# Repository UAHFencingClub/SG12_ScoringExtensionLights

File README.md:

# SG12_ScoringExtensionLights

A module for the [SG12 fencing scoring machine](https://www.blue-gauntlet.com/SG12-ST-MACHINE-w-score-and-time-and-remote_p_3799.html) that allows for 12V LED strips to be used as extension lights.

You can view the mirror on [CADLAB.io](https://cadlab.io/project/27194/main/files) if you want to see the schematic. < Needs to be updated, not sure why mirroring is not working.

# Wiring Diagram

Annocations and a wiring diagram can be found [here](Wiring.md)

# Parts (Haphazard)

Most things I got off amazon. I have not gotten all the connectors since not all are actually required. It depends on what you need. Look at the schematic to find out.

- IRF4905 MOSFET (Though probably most P Channel MOSFETs will do)
- Some sort of RJ45 (Ethernet) Connector (Don't get the ones with built in magnetics, those are usually a bit larger and are only for actual ethernet applications.
- Whatever 10k resistors you can find, the value really does not matter I would suggest something between 1k and 100k
- Some sort of barrel jack connector (Inner pin diameter of 2.1mm is more common than ones with 2.5mm inner pin diameter)
- PhoenixContact MSTBA 2,5 2-G-5,08 1x02 P5.08mm Horizontal
- Molex Mini-Fit Jr 5569 2x04 P4.20mm Horizontal
- Standard 2.54mm pin header

# Get PCBs

**Disclaimer: If ordering through their site, PCBWay will "donate 10% PCB and PCB assembly cost to" [me](https://github.com/QuantumEF)**

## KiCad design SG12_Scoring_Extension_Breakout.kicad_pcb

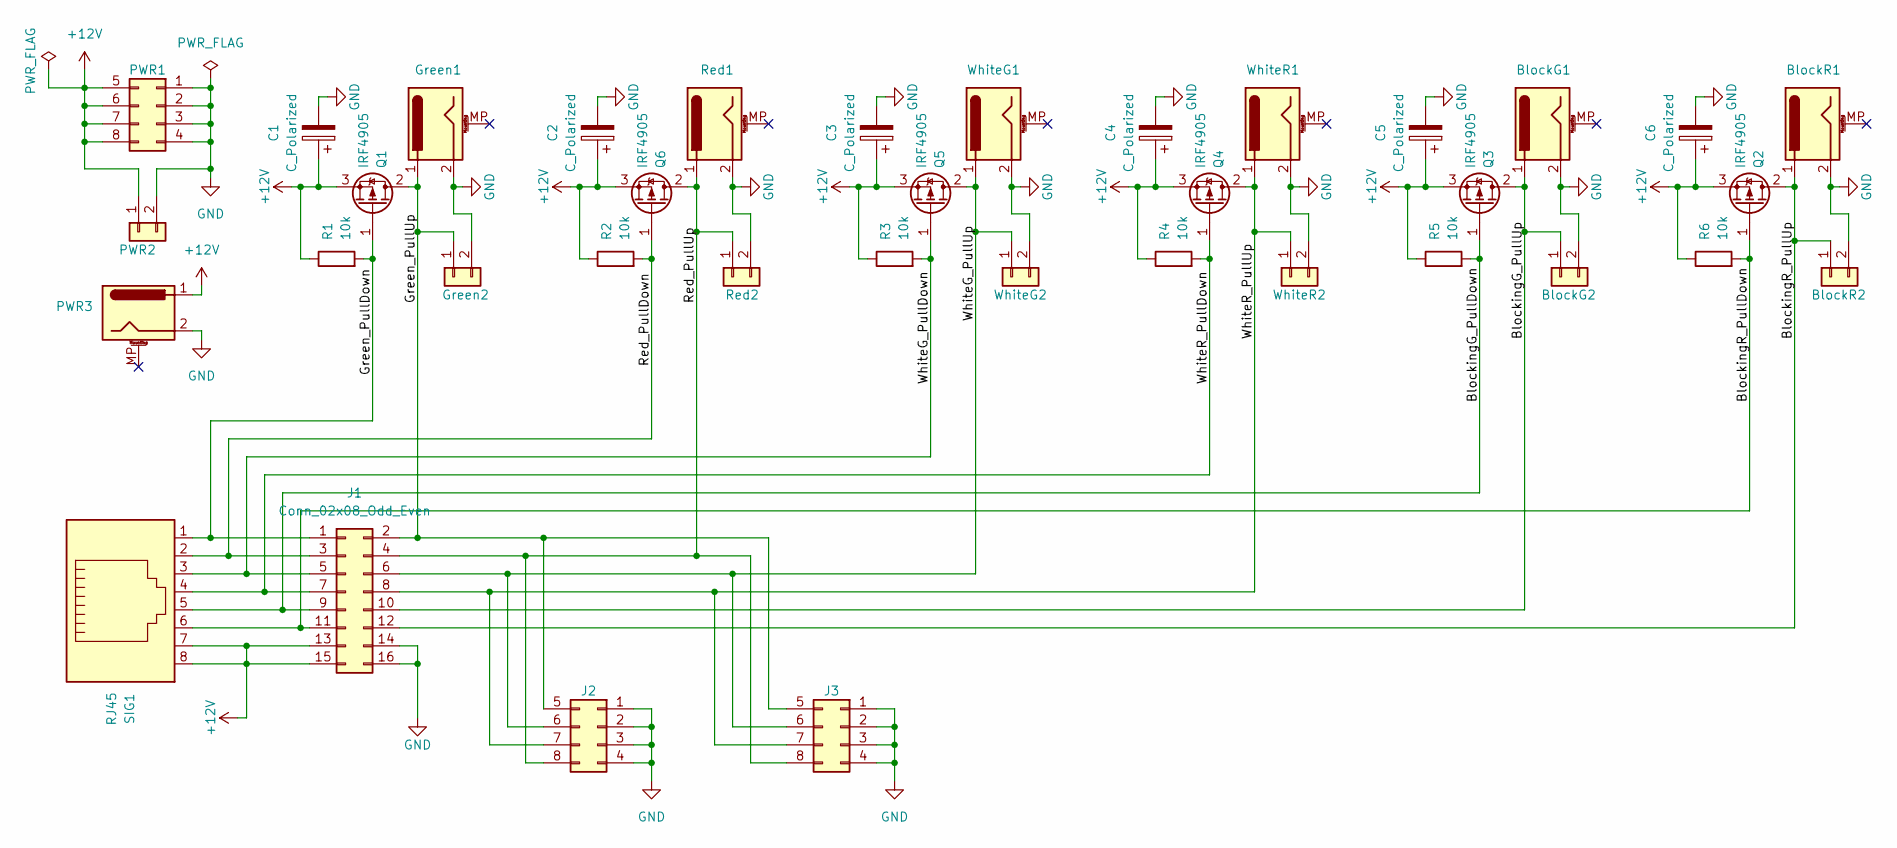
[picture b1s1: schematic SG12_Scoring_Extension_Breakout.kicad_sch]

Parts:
BlockG1: Barrel_Jack_MountingPin; BarrelJack_GCT_DCJ200-10-A_Horizontal
BlockG2: Conn_01x02; PhoenixContact_MSTBA_2,5_2-G-5,08_1x02_P5.08mm_Horizontal
BlockR1: Barrel_Jack_MountingPin; BarrelJack_GCT_DCJ200-10-A_Horizontal
BlockR2: Conn_01x02; PhoenixContact_MSTBA_2,5_2-G-5,08_1x02_P5.08mm_Horizontal
C1, C2, C3, C4, C5, C6: C_Polarized; CP_Radial_D6.3mm_P2.50mm
Green1: Barrel_Jack_MountingPin; BarrelJack_GCT_DCJ200-10-A_Horizontal
Green2: Conn_01x02; PhoenixContact_MSTBA_2,5_2-G-5,08_1x02_P5.08mm_Horizontal
J1: Conn_02x08_Odd_Even; PinHeader_2x08_P2.54mm_Vertical
J2, J3: Conn_02x04_Top_Bottom; Molex_Mini-Fit_Jr_5569-08A2_2x04_P4.20mm_Horizontal
PWR1: Conn_02x04_Top_Bottom; Molex_Mini-Fit_Jr_5569-08A2_2x04_P4.20mm_Horizontal
PWR2: Conn_01x02; PhoenixContact_MSTBA_2,5_2-G-5,08_1x02_P5.08mm_Horizontal
PWR3: Barrel_Jack_MountingPin; BarrelJack_GCT_DCJ200-10-A_Horizontal
Q1, Q2, Q3, Q4, Q5, Q6: IRF4905; TO-220-3_Vertical
R1, R2, R3, R4, R5, R6: 10k; R_Axial_DIN0207_L6.3mm_D2.5mm_P10.16mm_Horizontal
Red1: Barrel_Jack_MountingPin; BarrelJack_GCT_DCJ200-10-A_Horizontal
Red2: Conn_01x02; PhoenixContact_MSTBA_2,5_2-G-5,08_1x02_P5.08mm_Horizontal
SIG1: RJ45; RJ45_Amphenol_54602-x08_Horizontal
WhiteG1: Barrel_Jack_MountingPin; BarrelJack_GCT_DCJ200-10-A_Horizontal
WhiteG2: Conn_01x02; PhoenixContact_MSTBA_2,5_2-G-5,08_1x02_P5.08mm_Horizontal
WhiteR1: Barrel_Jack_MountingPin; BarrelJack_GCT_DCJ200-10-A_Horizontal
WhiteR2: Conn_01x02; PhoenixContact_MSTBA_2,5_2-G-5,08_1x02_P5.08mm_Horizontal

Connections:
+12V: C1.1, C2.1, C3.1, C4.1, C5.1, C6.1, J1.13, J1.15, PWR1.5, PWR1.6, PWR1.7, PWR1.8, PWR2.1, PWR3.1, Q1.3 (S), Q2.3 (S), Q3.3 (S), Q4.3 (S), Q5.3 (S), Q6.3 (S), R1.1, R2.1, R3.1, R4.1, R5.1, R6.1, SIG1.7, SIG1.8
/BlockingG_PullDown: J1.9, Q3.1 (G), R5.2, SIG1.5
/BlockingG_PullUp: BlockG1.1, BlockG2.1, J1.10, Q3.2 (D)
/BlockingR_PullDown: J1.11, Q2.1 (G), R6.2, SIG1.6
/BlockingR_PullUp: BlockR1.1, BlockR2.1, J1.12, Q2.2 (D)
/Green_PullDown: J1.1, Q1.1 (G), R1.2, SIG1.1
/Green_PullUp: Green1.1, Green2.1, J1.2, J2.5, J3.5, Q1.2 (D)
/Red_PullDown: J1.3, Q6.1 (G), R2.2, SIG1.2
/Red_PullUp: J1.4, J2.8, J3.8, Q6.2 (D), Red1.1, Red2.1
/WhiteG_PullDown: J1.5, Q5.1 (G), R3.2, SIG1.3
/WhiteG_PullUp: J1.6, J2.6, J3.6, Q5.2 (D), WhiteG1.1, WhiteG2.1
/WhiteR_PullDown: J1.7, Q4.1 (G), R4.2, SIG1.4
/WhiteR_PullUp: J1.8, J2.7, J3.7, Q4.2 (D), WhiteR1.1, WhiteR2.1
GND: BlockG1.2, BlockG2.2, BlockR1.2, BlockR2.2, C1.2, C2.2, C3.2, C4.2, C5.2, C6.2, Green1.2, Green2.2, J1.14, J1.16, J2.1, J2.2, J2.3, J2.4, J3.1, J3.2, J3.3, J3.4, PWR1.1, PWR1.2, PWR1.3, PWR1.4, PWR2.2, PWR3.2, Red1.2, Red2.2, WhiteG1.2, WhiteG2.2, WhiteR1.2, WhiteR2.2

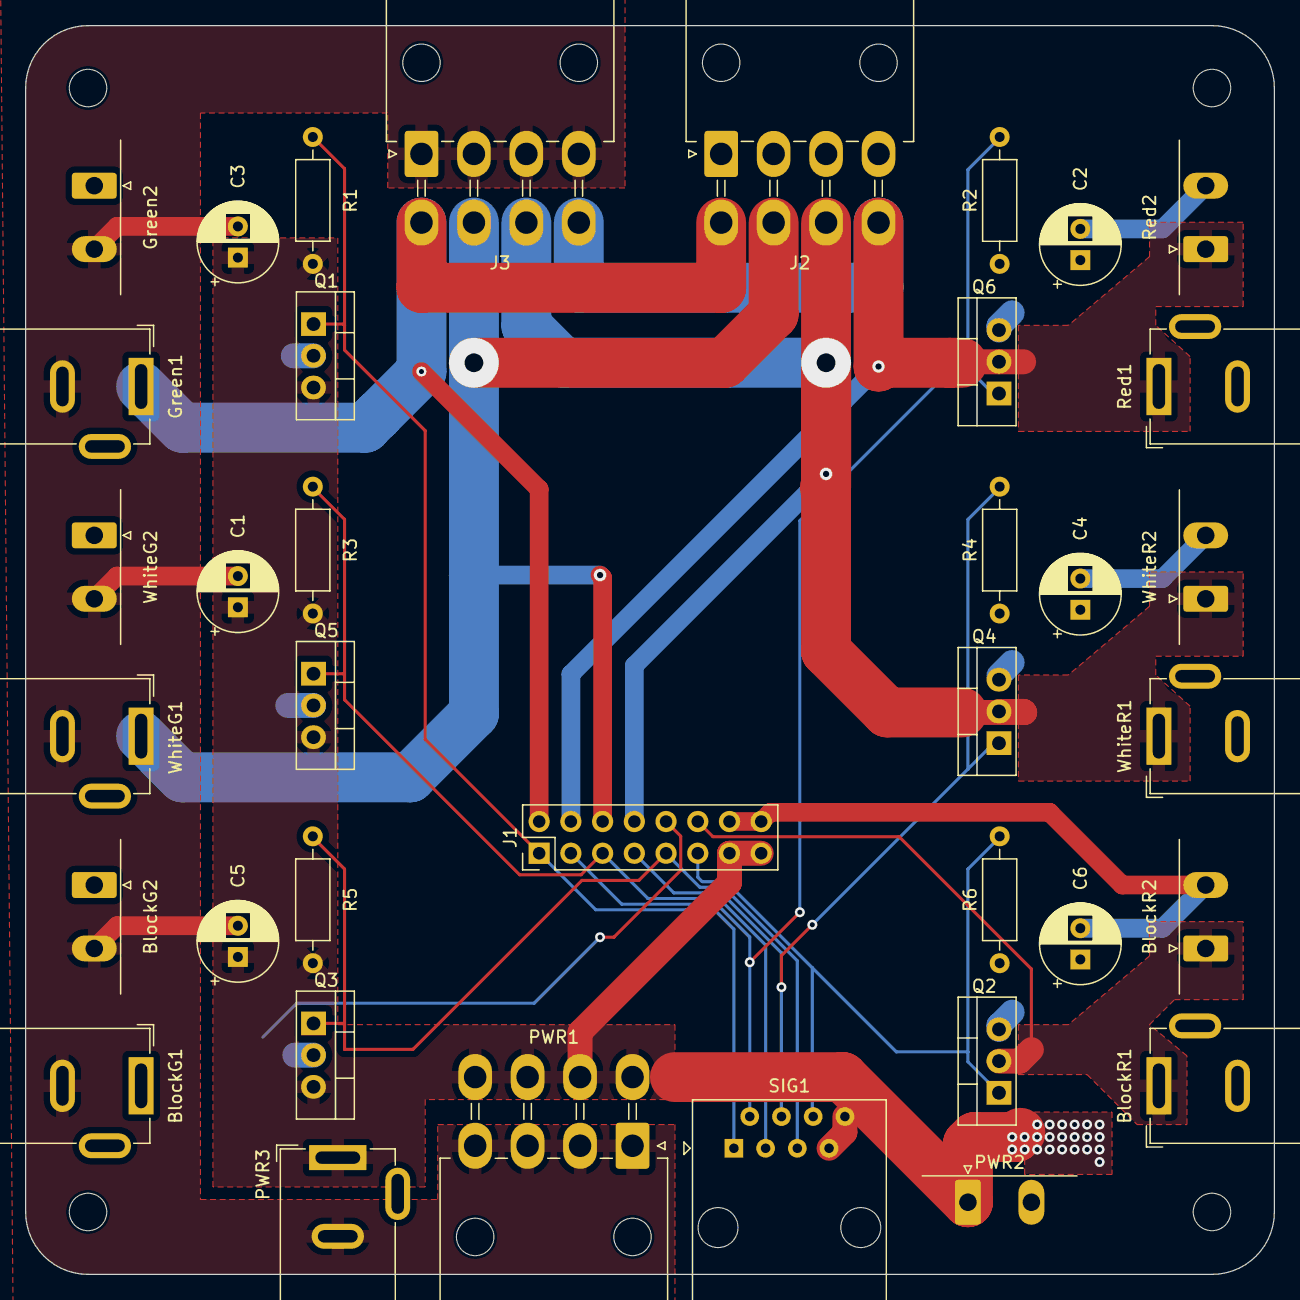
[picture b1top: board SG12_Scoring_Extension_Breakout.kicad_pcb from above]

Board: 2 copper layers, 100.0 x 100.0 mm, 37 parts (0 on the bottom side), 14 nets.

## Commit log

2023-09-07 Update to newer kicad version
2023-09-15 Updated and redid from scratch
2023-09-15 Removed old files and added gitignore
2023-09-15 Messed up a footprint
2023-09-15 WIP: PCB Layout, Items placed
2023-09-15 Some Initial PCB traces, will redo since I am not happy, and the scematic may be wrong
2023-09-15 Added decoupling capacitors and extra header
2023-09-16 Added footprints
2023-09-16 Some Initial PCB Layout
2023-09-16 Finished up initial routing, need to check rules
2023-09-16 Removed off-board silkscreen
2023-09-16 added manufacturing folder to gitignore
2023-09-16 Added silkscreen text
2023-09-16 More silkscreen
2023-09-16 Updated routing and RJ45 footprint
2023-09-16 Added liscense to silk screen
2023-09-17 Minor routing adjustments
2023-09-17 More trace finetuning because I am bored
2023-09-17 Added more overhang for connectors
2023-09-17 Forgot to move labels
2023-09-17 Added 3d models for barrel jacks
2023-09-17 Various changes I guess
2023-09-17 Export of initial 3d model
2023-09-18 Case Design
2023-09-18 Updated case lid
2023-09-19 Updated lid design, forgot to push freecad model
2023-09-21 updated pcb dimensions and silkscreen
2023-09-21 various updates
2023-09-21 Updated 3d model
2023-09-21 Updated case
2023-09-26 messing around with barrel jack models
2023-09-26 updated some silkscreen and trace widths
2023-10-06 Updated schematic with extra connections
2023-10-06 Forgot connector
2023-10-06 Rough component placement
2023-10-06 Added mouting holes, iteration 2
2023-10-06 Flipped connections on mini-fit connectors to match EPS12V
2023-10-06 Very nitpicky positioning on the Red and Green connectors
2023-10-06 Very nitpicky mofet and resistor placement
2023-10-06 Initial footprint placement
2023-10-06 Switched connections for easier routing later
2023-10-06 Switched more connections for easier routing later
2023-10-06 Some initial routing
2023-10-11 Finished routing
2023-10-11 Routing adjustments
2023-10-11 Schematic Symbol Names
2023-10-11 Silkscreen Labels
2023-10-11 Ignoring sinkscreen clippings
2023-10-11 Re-added thermal reliefs
2023-10-11 Updated some via sizes
2023-10-11 Power flags for ERC checker
2023-10-12 Footprint modifications
2023-10-13 moved power vias
2024-03-25 first manufactured board
2024-03-25 Nice picture
2024-03-30 Update README.md with PCBWay
2024-03-30 Update README.md more percise
2025-04-10 Some additional images for documentation
2025-04-10 Initial WiringDiagrams
2025-04-10 Wiring Diagram updates and documentation
2025-04-10 Minor Fix for Wiring diagrams
2025-04-13 More images
